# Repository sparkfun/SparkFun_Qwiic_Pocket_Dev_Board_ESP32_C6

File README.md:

SparkFun Qwiic Pocket Development Board - ESP32-C6
========================================

[*SparkFun Qwiic Pocket Development Board - ESP32-C6 (DEV-22925)*](https://www.sparkfun.com/products/22925)

The SparkFun Qwiic Pocket Development Board - ESP32-C6 is designed to fit in the 1"x1" Qwiic standard size making it easy to add a powerful wireless development platform that stacks into any existing project using the [Qwiic ecosystem](https://www.sparkfun.com/qwiic). It features the ESP32-C6 Mini-1 module from espressif<sup>&trade;</sup>. We designed this board with components on both sides of the PCB to squeeze as many features as possible into its tiny footprint including a USB-C connector, Qwiic connector, 2-pin JST battery connector with on-board charging circuit, as well as two buttons for Reset and Boot. The design also works to optimize power consumption and in our testing we measured total current consumption by the board to be ~14&micro;A in Deep Sleep mode making it a great fit for remote, battery-powered applications.

Repository Contents
-------------------

* **/Documents** - Datasheets, additional product information 
* **/Examples** - Example code 
* **/Hardware** - Eagle design files (.brd, .sch)
* **/Production** - Production panel files (.brd)
* **/docs** - Documentation files for the Qwiic Pocket Development Board - ESP32-C6

Documentation
--------------
* **[Hookup Guide](https://sparkfun.github.io/SparkFun_Qwiic_Pocket_Dev_Board_ESP32_C6)** - Basic hookup guide for the Qwiic Pocket Development Board ESP32-C6.
* **[SparkFun Fritzing repo](https://github.com/sparkfun/Fritzing_Parts)** - Fritzing diagrams for SparkFun products.

Product Versions
----------------
* [DEV-22925](https://www.sparkfun.com/products/22925) - Initial release

License Information
-------------------

This product is _**open source**_! 

Please review the LICENSE.md file for license information. 

If you have any questions or concerns on licensing, please contact technical support on our [SparkFun forums](https://forum.sparkfun.com/viewforum.php?f=152).

Distributed as-is; no warranty is given.

- Your friends at SparkFun.

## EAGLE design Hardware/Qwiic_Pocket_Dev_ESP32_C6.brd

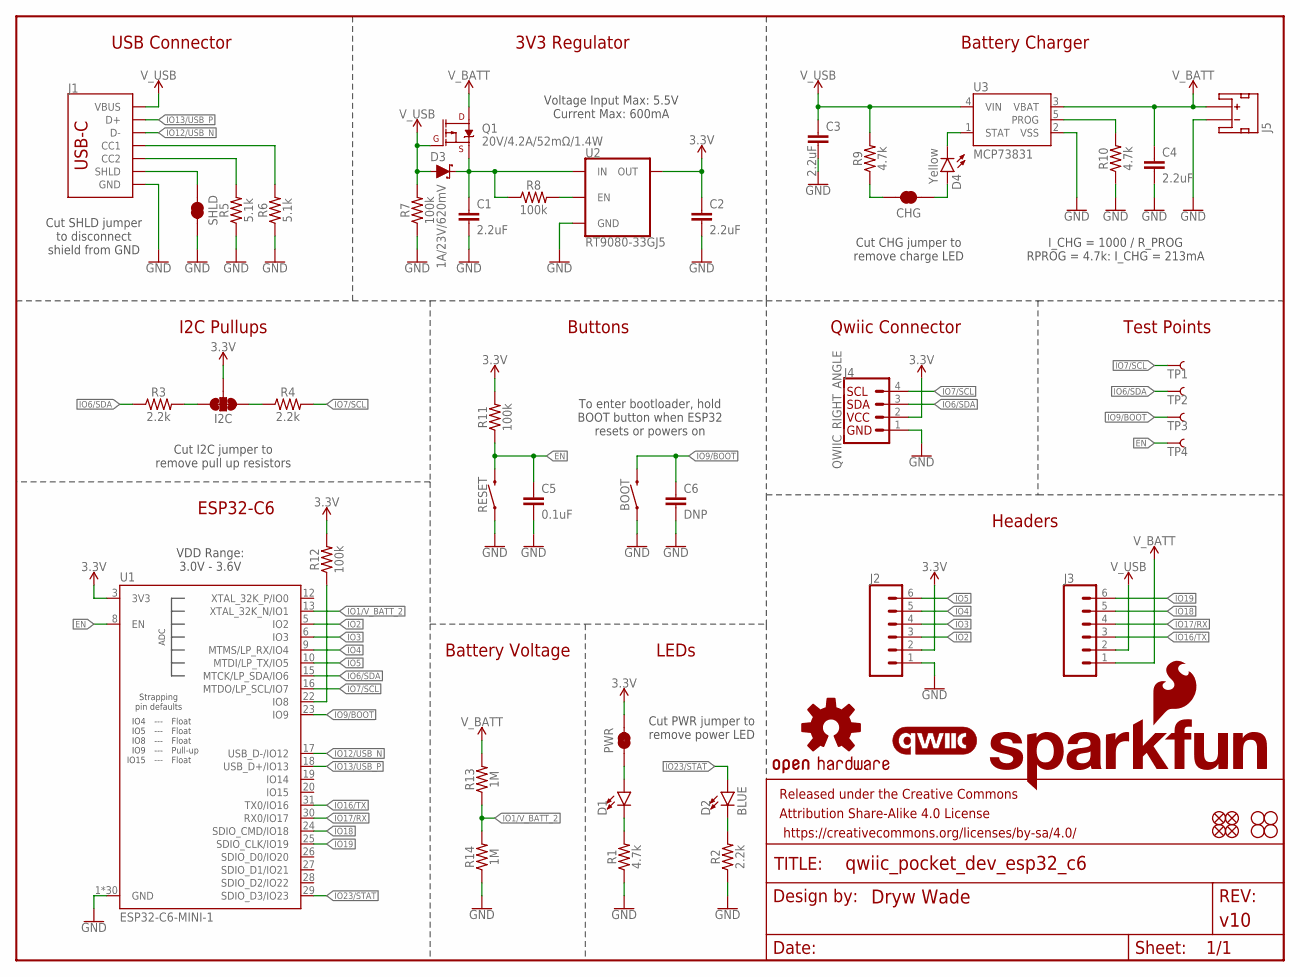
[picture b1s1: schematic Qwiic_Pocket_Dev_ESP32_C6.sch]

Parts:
BOOT: MOMENTARY-SWITCH-SPST-SMD-4.6X2.8MM; TACTILE_SWITCH_SMD_4.6X2.8MM
C1, C2, C3, C4: 2.2uF; 0402-TIGHT
C5: 0.1uF; 0402-TIGHT
C6: DNP; 0402-TIGHT
CHG: JUMPER-SMT_2_NC_TRACE_SILK; SMT-JUMPER_2_NC_TRACE_SILK
D1: LED-RED_0603-KB; LED-0603
D2: BLUE; LED-0603
D3: 1A/23V/620mV; SOD-323
D4: Yellow; LED-0603
FD1, FD2, FD3, FD4: FIDUCIALUFIDUCIAL; FIDUCIAL-MICRO
FRAME1: FRAME-LETTER; CREATIVE_COMMONS
H1, H2, H3, H4: STAND-OFF
I2C: JUMPER-SMT_3_2-NC_TRACE_SILK; SMT-JUMPER_3_2-NC_TRACE_SILK
J1: USB Female Type C Connector; USB-C-16P_4LAYER-PADS
J2, J3: CONN_06NO_SILK_NO_POP; 1X06_NO_SILK
J4: QWIIC_RIGHT_ANGLE; JST04_1MM_RA
J5: JST_2MM_MALE; JST-2-SMD
LOGO1: SFE_LOGO_NAME_FLAMEBLANK; BLANK
LOGO2: OSHW-LOGOS; OSHW-LOGO-S
LOGO3: QWIIC_LOGO_3MM; QWIIC_3MM
PWR: JUMPER-SMT_2_NC_TRACE_SILK; SMT-JUMPER_2_NC_TRACE_SILK
Q1: 20V/4.2A/52mΩ/1.4W; SOT23-3
R1, R9, R10: 4.7k; 0402-TIGHT
R2, R3, R4: 2.2k; 0402-TIGHT
R5, R6: 5.1k; 0402-TIGHT
R7, R8, R11, R12: 100k; 0402-TIGHT
R13, R14: 1M; 0402-TIGHT
RESET: MOMENTARY-SWITCH-SPST-SMD-4.6X2.8MM; TACTILE_SWITCH_SMD_4.6X2.8MM
SHLD: JUMPER-SMT_2_NC_TRACE_SILK; SMT-JUMPER_2_NC_TRACE_SILK
TP1, TP2, TP3, TP4: TEST-POINT3; PAD.03X.03
U1: ESP32-C6-MINI-1
U2: RT9080-33GJ5; SOT23-5
U3: MCP73831; SOT23-5

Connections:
3.3V: C2.1, I2C.2, J2.2, J4.2, PWR.2, R11.2, R12.2, U1.3 (3V3), U2.5 (OUT)
EN: C5.1, R11.1, RESET.3 (2), RESET.4 (2), TP4.1, U1.8 (EN)
GND: BOOT.1, BOOT.2 (1), C1.2, C2.2, C3.2, C4.2, C5.2, C6.2, J1.GND, J1.GND2 (GND), J2.1, J4.1, J5.1 (-), R1.1, R2.1, R5.1, R6.1, R7.1, R10.1, R14.1, RESET.1, RESET.2 (1), SHLD.2, U1.1 (GND), U1.2 (GND), U1.11 (GND), U1.14 (GND), U1.36 (GND), U1.37 (GND), U1.38 (GND), U1.39 (GND), U1.40 (GND), U1.41 (GND), U1.42 (GND), U1.43 (GND), U1.44 (GND), U1.45 (GND), U1.46 (GND), U1.47 (GND), U1.48 (GND), U1.49.1 (GND), U1.49.2 (GND), U1.49.3 (GND), U1.49.4 (GND), U1.49.5 (GND), U1.49.6 (GND), U1.49.7 (GND), U1.49.8 (GND), U1.49.9 (GND), U1.50 (GND), U1.51 (GND), U1.52 (GND), U1.53 (GND), U2.2 (GND), U3.2 (VSS)
IO1/V_BATT_2: R13.1, R14.2, U1.13 (XTAL_32K_N/IO1)
IO2: J2.3, U1.5 (IO2)
IO3: J2.4, U1.6 (IO3)
IO4: J2.5, U1.9 (MTMS/LP_RX/IO4)
IO5: J2.6, U1.10 (MTDI/LP_TX/IO5)
IO6/SDA: J4.3, R3.1, TP2.1, U1.15 (MTCK/LP_SDA/IO6)
IO7/SCL: J4.4, R4.2, TP1.1, U1.16 (MTDO/LP_SCL/IO7)
IO9/BOOT: BOOT.3 (2), BOOT.4 (2), C6.1, TP3.1, U1.23 (IO9)
IO12/USB_N: J1.A7 (D-), J1.B7 (D-), U1.17 (USB_D-/IO12)
IO13/USB_P: J1.A6 (D+), J1.B6 (D+), U1.18 (USB_D+/IO13)
IO16/TX: J3.3, U1.31 (TX0/IO16)
IO17/RX: J3.4, U1.30 (RX0/IO17)
IO18: J3.5, U1.24 (SDIO_CMD/IO18)
IO19: J3.6, U1.25 (SDIO_CLK/IO19)
IO23/STAT: D2.A, U1.29 (SDIO_D3/IO23)
unnamed: D1.C, R1.2
unnamed: D1.A, PWR.1
unnamed: D2.C, R2.2
unnamed: I2C.3, R3.2
unnamed: I2C.1, R4.1
unnamed: R8.2, U2.3 (EN)
unnamed: J1.B5 (CC2), R5.2
unnamed: J1.A5 (CC1), R6.2
unnamed: C1.1, D3.C, Q1.2 (S), R8.1, U2.1 (IN)
unnamed: D4.C, U3.1 (STAT)
unnamed: CHG.1, D4.A
unnamed: CHG.2, R9.1
unnamed: R10.2, U3.5 (PROG)
unnamed: R12.1, U1.22 (IO8)
SHLD: J1.SHLD1 (SHLD), J1.SHLD2 (SHLD), J1.SHLD3 (SHLD), J1.SHLD4 (SHLD), SHLD.1
V_BATT: C4.1, J3.1, J5.2 (+), Q1.3 (D), R13.2, U3.3 (VBAT)
V_USB: C3.1, D3.A, J1.VBUS1 (VBUS), J1.VBUS2 (VBUS), J3.2, Q1.1 (G), R7.2, R9.2, U3.4 (VIN)

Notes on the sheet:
USB Connector
3V3 Regulator
Battery Charger
Qwiic Connector
Headers
LEDs
Buttons
I2C Pullups
ESP32-C6
VDD Range: 3.0V - 3.6V
Cut I2C jumper to remove pull up resistors
Cut PWR jumper to remove power LED
Cut CHG jumper to remove charge LED
I_CHG = 1000 / R_PROG RPROG = 4.7k: I_CHG = 213mA
Test Points
Voltage Input Max: 5.5V Current Max: 600mA
To enter bootloader, hold BOOT button when ESP32 resets or powers on
Cut SHLD jumper to disconnect shield from GND
Battery Voltage

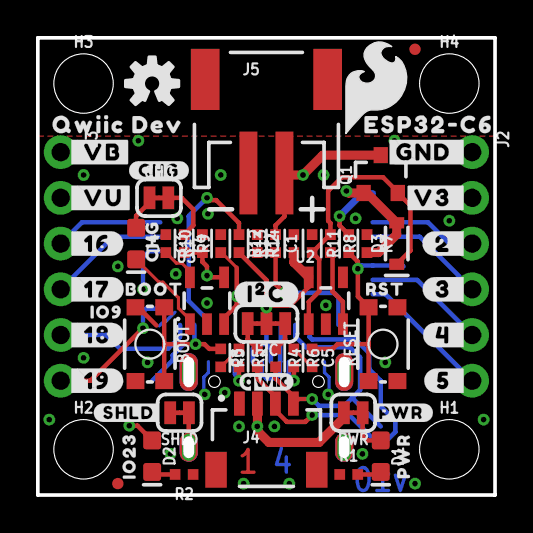
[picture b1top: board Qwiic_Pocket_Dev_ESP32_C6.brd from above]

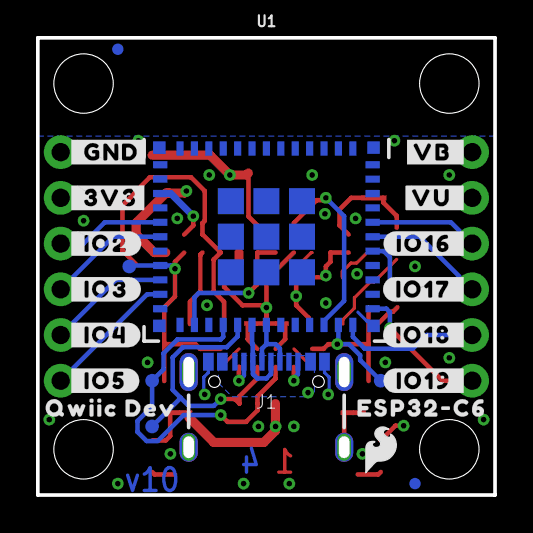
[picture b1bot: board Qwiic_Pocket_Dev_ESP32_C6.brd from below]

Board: 4 copper layers, 25.4 x 25.4 mm, 96 parts (23 on the bottom side), 35 nets.

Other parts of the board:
U$1: #_GND#0
U$2: #_3V3#0
U$3: #V3_#0
U$5: #GND_#0
U$6: SFE_LOGO_FLAME_.2
U$7: #VU_#0
U$8: #_VB#0
U$9, U$25: QWIIC_DEV0
U$10: SFE_LOGO_FLAME_.1
U$11, U$12: ESP32#C633
U$13: #_IO5#0
U$14: #_IO4#0
U$15: #_IO3#0
U$16: #_IO2#0
U$17: #IO16_#0
U$18: #IO17_#0
U$19: #IO18_#0
U$20: #IO19_#0
U$21: #5_#0
U$22: #4_#0
U$23: #I�C#0
U$24: ORDERING_INSTRUCTIONS
U$26: #PWR#0
U$27: #SHLD#0
U$28: IO230
U$30: PWR0
U$31: #CHG#0
U$32: CHG0
U$33: BOOT0
U$34: RST0
U$35: IO90
U$36: #VB_#0
U$37: #_VU#0
U$38: #3_#0
U$39: #2_#0
U$40: #_16#0
U$41: #_17#0
U$42: #_18#0
U$43: #_19#0

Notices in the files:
parts and their libraries:
SparkFun-Hardware: Licensing: Creative Commons ShareAlike 4.0 International - https://creativecommons.org/licenses/by-sa/4.0
SparkFun-Aesthetics: Released under the Creative Commons Attribution Share-Alike 4.0 License
SparkFun-Aesthetics: https://creativecommons.org/licenses/by-sa/4.0
